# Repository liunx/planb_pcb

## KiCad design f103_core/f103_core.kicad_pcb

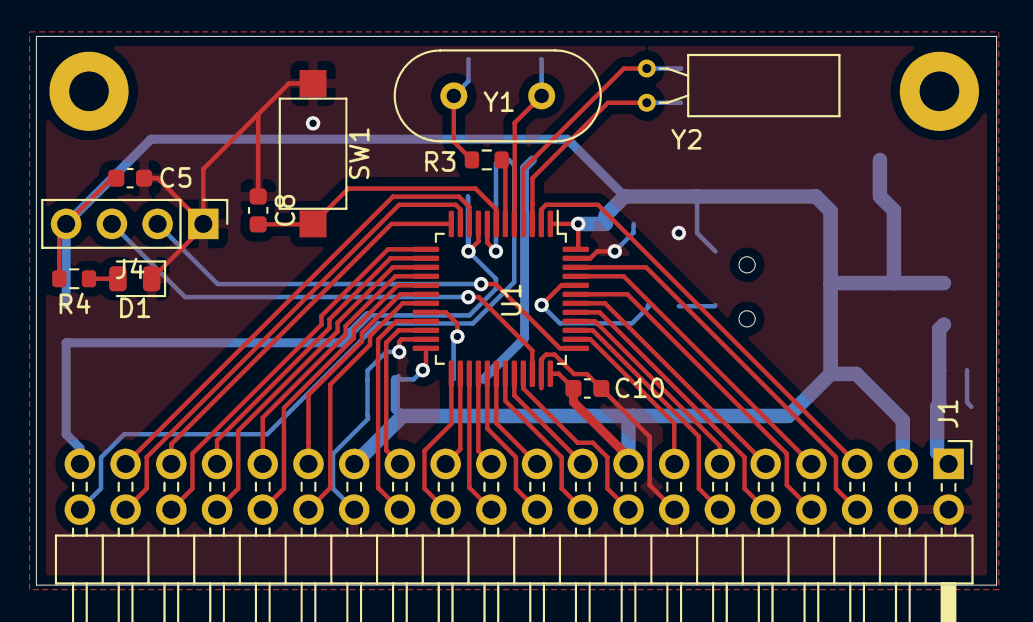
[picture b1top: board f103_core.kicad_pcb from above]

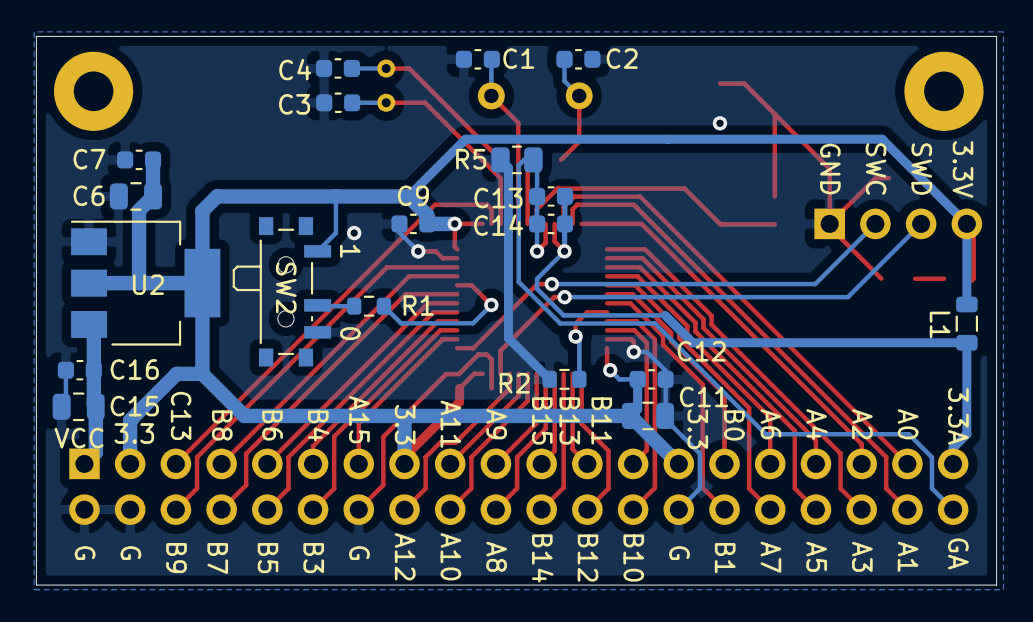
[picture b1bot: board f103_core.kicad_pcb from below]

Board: 2 copper layers, 53.3 x 30.5 mm, 32 parts (19 on the bottom side), 47 nets.

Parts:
1: MountingHole_2.2mm_M2_Pad
C1, C2: 20pF; C_0603_1608Metric
C3, C4: 10pF; C_0603_1608Metric
C5, C7, C8, C9, C10, C12, C16: 100nF; C_0603_1608Metric
C6, C15: 10uF; C_0805_2012Metric
C11: 4.7uF; C_0805_2012Metric
C13: 1uF; C_0603_1608Metric
C14: 10nF; C_0603_1608Metric
D1: LED; LED_0805_2012Metric
J1: Conn_02x20_Odd_Even; PinHeader_2x20_P2.54mm_Horizontal
J4: Conn_01x04; PinHeader_1x04_P2.54mm_Vertical
L1: 10uH; L_0805_2012Metric
R1, R2: 10K; R_0603_1608Metric
R3: 390; R_0603_1608Metric
R4: 510R; R_0603_1608Metric
R5: 0R; R_0805_2012Metric
SW1: SW_Push; SW_SPST_CK_RS282G05A3
SW2: SW_DPDT_x2; SW_SPDT_PCM12
U1: STM32F103C6Tx; LQFP-48_7x7mm_P0.5mm
U2: AMS1117-3.3; SOT-223-3_TabPin2
Y1: 8M; Crystal_HC49-4H_Vertical
Y2: 32.768; Crystal_C38-LF_D3.0mm_L8.0mm_Horizontal

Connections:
+3.3VA: C13.1, C14.1, J1.39, L1.2, U1.9
+3V3: C5.1, C6.1, C7.1, C9.1, C10.1, C11.1, C12.1, J1.3, J1.15, J1.27, J4.4, L1.1, R4.2, SW2.1, U1.1, U1.24, U1.36, U1.48, U2.2
/BOOT0: R1.2, U1.44
/BOOT1: R2.1, U1.20
/PA0: J1.37, U1.10
/PA1: J1.38, U1.11
/PA2: J1.35, U1.12
/PA3: J1.36, U1.13
/PA4: J1.33, U1.14
/PA5: J1.34, U1.15
/PA6: J1.31, U1.16
/PA7: J1.32, U1.17
/PA8: J1.20, U1.29
/PA9: J1.19, U1.30
/PA10: J1.18, U1.31
/PA11: J1.17, U1.32
/PA12: J1.16, U1.33
/PA15: J1.13, U1.38
/PB0: J1.29, U1.18
/PB1: J1.30, U1.19
/PB3: J1.12, U1.39
/PB4: J1.11, U1.40
/PB5: J1.10, U1.41
/PB6: J1.9, U1.42
/PB7: J1.8, U1.43
/PB8: J1.7, U1.45
/PB9: J1.6, U1.46
/PB10: J1.26, U1.21
/PB11: J1.25, U1.22
/PB12: J1.24, U1.25
/PB13: J1.23, U1.26
/PB14: J1.22, U1.27
/PB15: J1.21, U1.28
/PC13: J1.5, U1.2
/RCC_OSC32_IN: C3.2, U1.3, Y2.1
/RCC_OSC32_OUT: C4.2, U1.4, Y2.2
/RCC_OSC_IN: C1.2, U1.5, Y1.1
/RCC_OSC_OUT: R3.2, U1.6
/SYS_JTCK-SWCL: J4.2, U1.37
/SYS_JTMS-SWDIO: J4.3, U1.34
GND: C1.1, C2.1, C3.1, C4.1, C5.2, C6.2, C7.2, C8.2, C9.2, C10.2, C11.2, C12.2, C15.2, C16.2, D1.1, J1.2, J1.4, J1.14, J1.28, J4.1, R2.2, R5.1, SW1.1, SW2.3, U1.23, U1.35, U1.47, U2.1
GNDA: C13.2, C14.2, J1.40, R5.2, U1.8
unnamed: C2.2, R3.1, Y1.2
unnamed: D1.2, R4.1
unnamed: R1.1, SW2.2
RESET: C8.1, SW1.2, U1.7
VCC: C15.1, C16.1, J1.1, U2.3

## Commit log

2022-06-25 Add f103c6tx_core board.
2022-06-27 Update pcb for f103_core.
2022-06-29 Update f103_core board.
